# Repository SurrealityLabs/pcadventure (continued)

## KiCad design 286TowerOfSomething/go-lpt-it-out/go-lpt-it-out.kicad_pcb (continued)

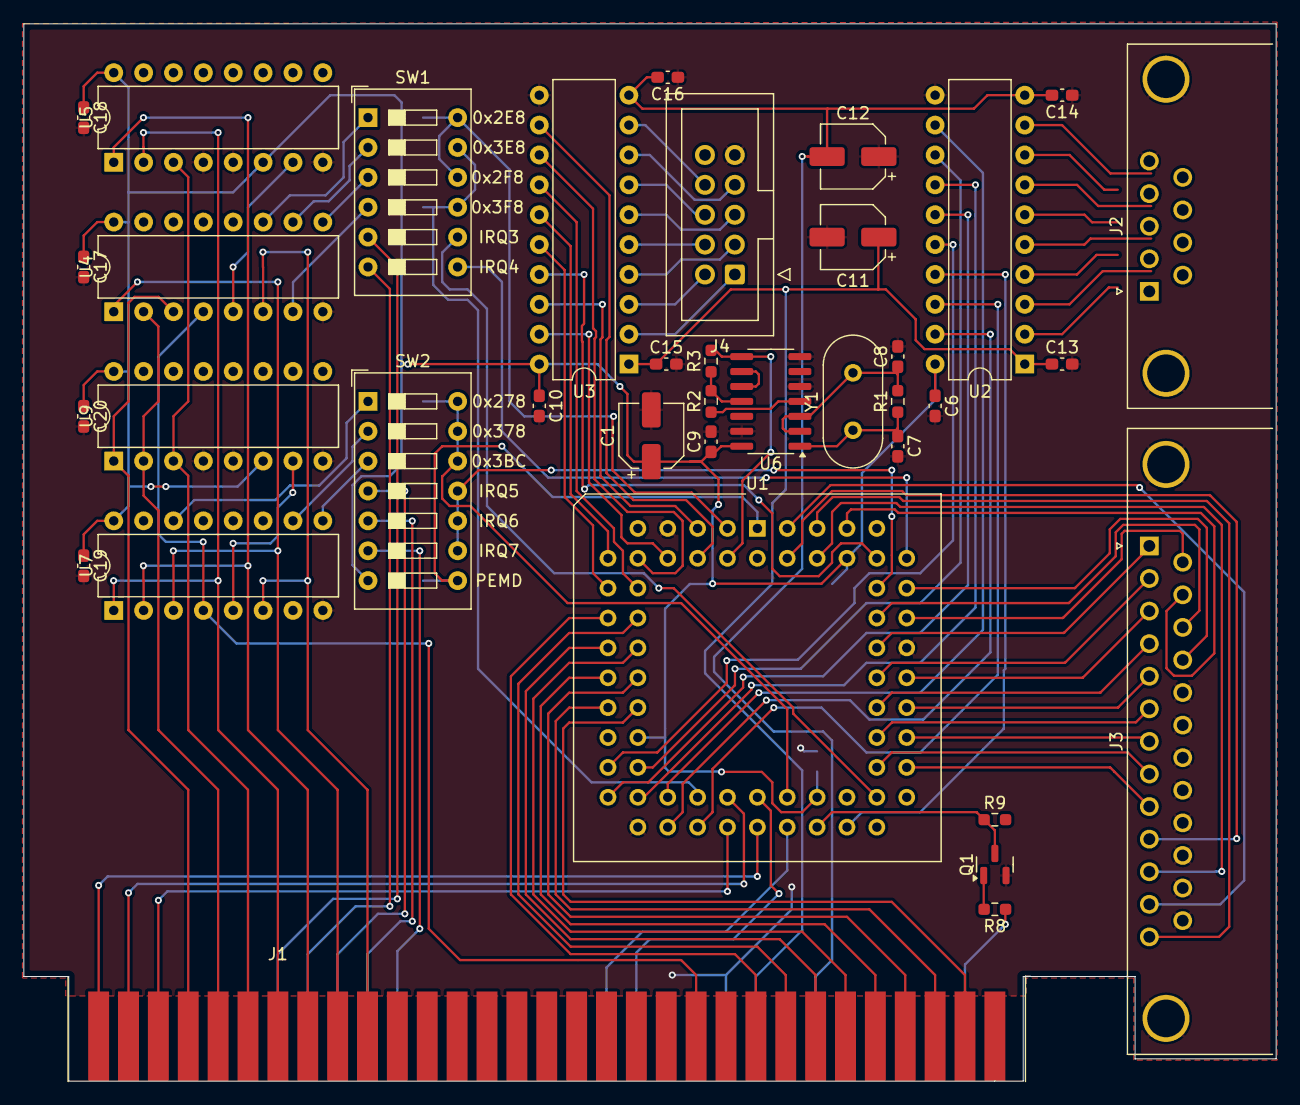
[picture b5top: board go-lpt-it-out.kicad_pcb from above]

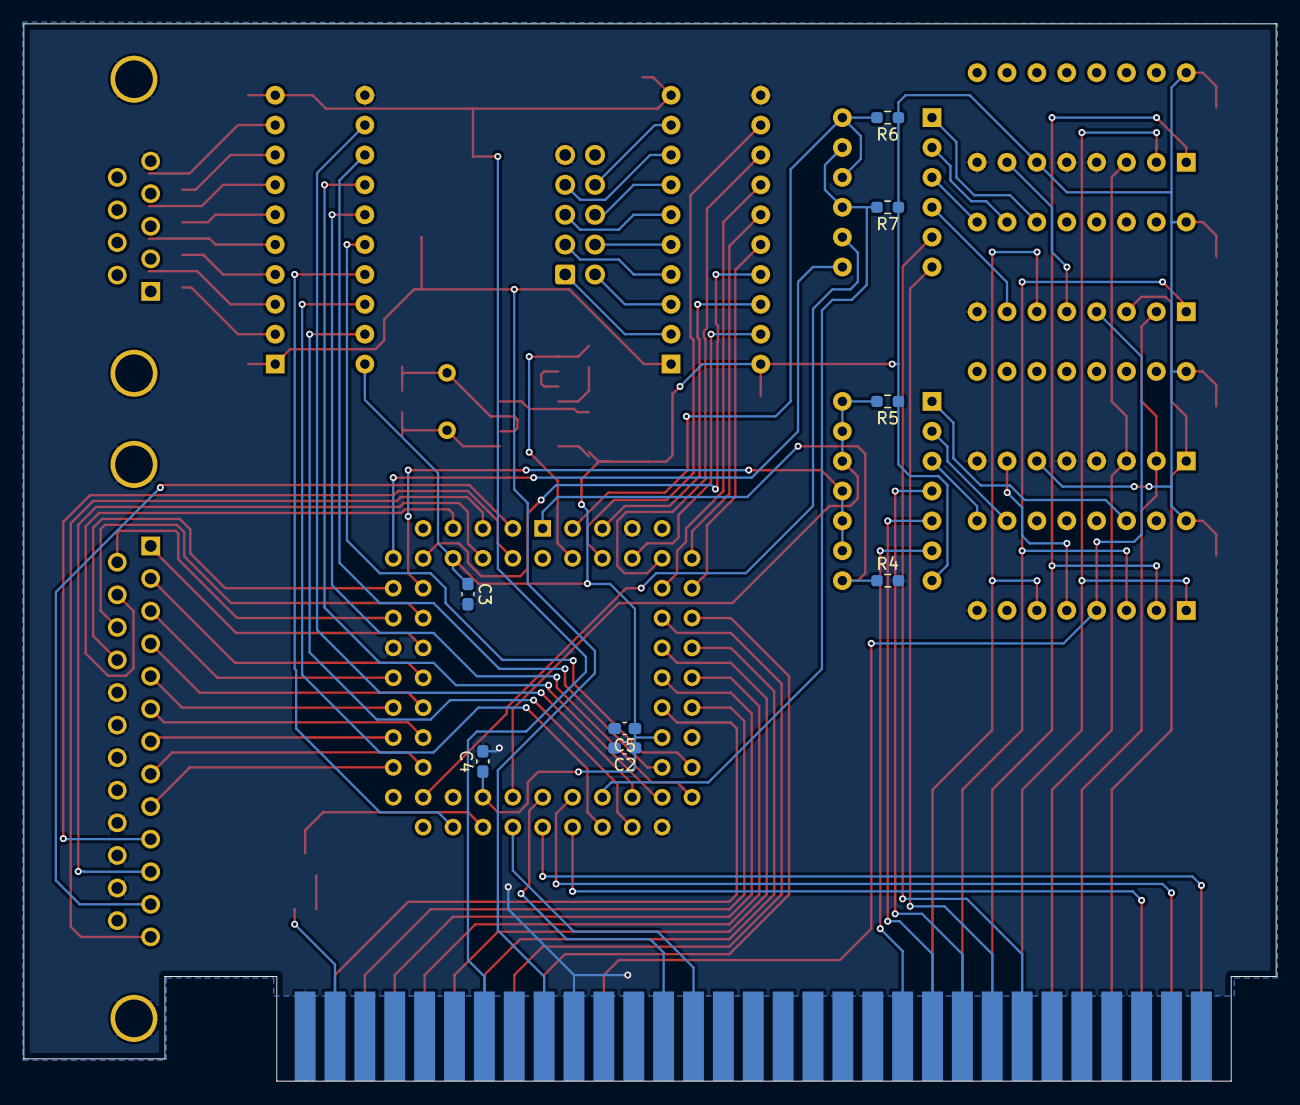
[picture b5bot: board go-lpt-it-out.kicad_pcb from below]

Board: 2 copper layers, 106.5 x 89.9 mm, 45 parts (8 on the bottom side), 104 nets.
